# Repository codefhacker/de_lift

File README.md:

# de_lift
Site voor het bewaren van alle bestanden voor de lift

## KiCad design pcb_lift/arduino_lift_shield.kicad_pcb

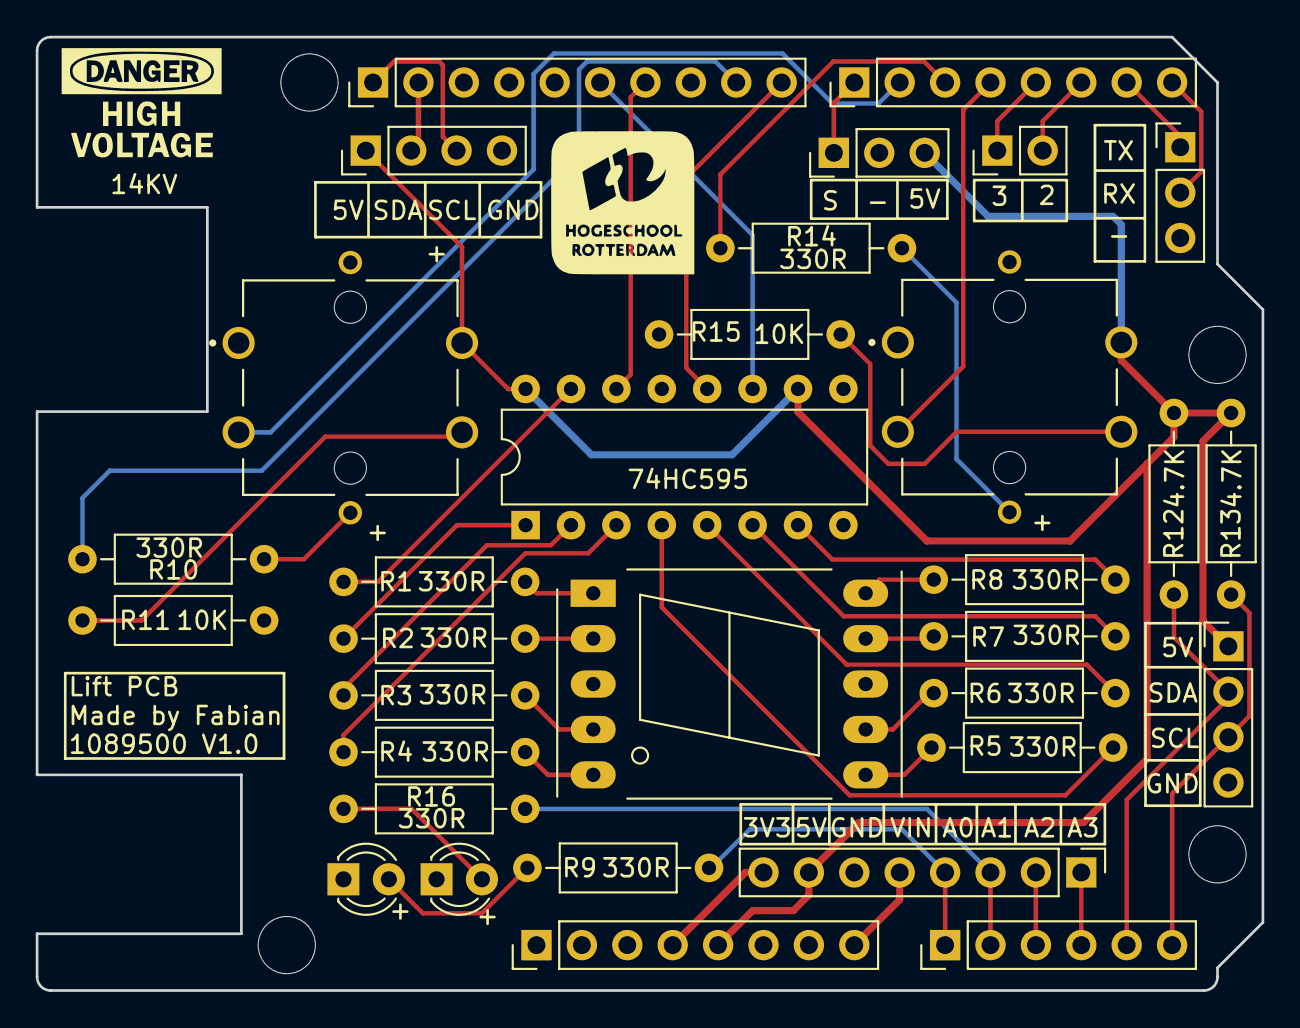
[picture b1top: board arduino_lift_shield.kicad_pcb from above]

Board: 2 copper layers, 68.6 x 53.3 mm, 36 parts (0 on the bottom side), 46 nets.

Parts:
D1, D2: LED; LED_D3.0mm
J1: Power; PinHeader_1x08_P2.54mm_Vertical
J2: Digital/PWM; PinHeader_1x10_P2.54mm_Vertical
J3: Analog; PinHeader_1x06_P2.54mm_Vertical
J4: Digital/PWM; PinHeader_1x08_P2.54mm_Vertical
J5, J10: Conn_01x04_Pin; PinHeader_1x04_P2.54mm_Vertical
J6, J9: Conn_01x03_Pin; PinHeader_1x03_P2.54mm_Vertical
J7: Conn_01x08_Pin; PinHeader_1x08_P2.54mm_Vertical
J11: Conn_01x02_Pin; PinHeader_1x02_P2.54mm_Vertical
MH1, MH2, MH3, MH4: MountingHole_3.2mm
R1, R2, R3, R4, R5, R6, R7, R8, R9, R10, R14, R16: 330R; R_Axial_DIN0207_L6.3mm_D2.5mm_P10.16mm_Horizontal
R11, R15: 10K; R_Axial_DIN0207_L6.3mm_D2.5mm_P10.16mm_Horizontal
R12, R13: 4.7K; R_Axial_DIN0207_L6.3mm_D2.5mm_P10.16mm_Horizontal
S1, S2: TSD1265; SW_TSD1265
U1: 74HC595; DIP-16_W7.62mm
U2: SM420561N; 7SegmentLED_LTS6760_LTS6780

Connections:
+3V3: J1.4, J7.8
+5V: J1.5, J5.1, J7.7, J9.3, J10.1, R12.2, R13.2, S1.D, S2.D, U1.10 (~SRCLR), U1.16 (VCC)
/2: J4.6, J11.2
/4: J4.4, S2.A
/7: J4.1, J9.1
/8: J2.10, U1.12 (RCLK)
/12: J2.6, U1.11 (SRCLK)
/*3: J4.5, J11.1
/*5: J4.3, R14.1
/*6: J4.2, S1.A
/*9: J2.9, R10.1
/*11: J2.7, U1.14 (SER)
/A0: J3.1, J7.4, R9.1
/A1: J3.2, J7.3, R16.1
/A2: J3.3, J7.2
/A3: J3.4, J7.1
/RX/0: J4.8, J6.2
/SCL2: J2.1, J5.3
/SCL/A5: J3.6, J10.3, R13.1
/SDA2: J2.2, J5.2
/SDA/A4: J3.5, J10.2, R12.1
/TX/1: J4.7, J6.1
GND: D1.1 (K), D2.1 (K), J1.6, J1.7, J2.4, J5.4, J6.3, J7.6, J9.2, J10.4, R11.2, R15.2, S1.F, S2.F, U1.8 (GND), U1.13 (~OE), U2.3 (CC), U2.8 (CC)
unnamed: D1.2 (A), R9.2
unnamed: D2.2 (A), R16.2
unnamed: R10.2, S1.E
unnamed: R11.1, S1.C
unnamed: R14.2, S2.E
unnamed: R15.1, S2.C
unnamed: R1.1, U1.15 (QA)
unnamed: R2.1, U1.1 (QB)
unnamed: R3.1, U1.2 (QC)
unnamed: R4.1, U1.3 (QD)
unnamed: R5.1, U1.4 (QE)
unnamed: R6.1, U1.5 (QF)
unnamed: R7.1, U1.6 (QG)
unnamed: R8.1, U1.7 (QH)
Pin_1: R1.2, U2.1 (E)
Pin_2: R2.2, U2.2 (D)
Pin_3: R3.2, U2.4 (C)
Pin_4: R4.2, U2.5 (DP)
Pin_5: R5.2, U2.6 (B)
Pin_6: R6.2, U2.7 (A)
Pin_7: R7.2, U2.9 (F)
Pin_8: R8.2, U2.10 (G)
VCC: J1.8, J7.5

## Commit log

2024-09-26 Create knop Arduino
2024-09-26 Rename knop Arduino to knop_led/knop_Arduino.ino
2024-10-10 Proof of concept interrupt
2024-10-17 prototype queue system
2024-10-17 determineDestination
2024-10-24 prot
2024-10-24 aaaa
2024-10-24 reworked without vectors
2024-10-24 Revert "Update main_master.ino"
    This reverts commit 14befe3b8252d7612847a0a98ab4e78e82f8f75f.
2024-10-24 [WIP] Movequeue 0.0.0.1
2024-11-11 Create Ontwerp_machinekamer
2024-11-11 Create PcbCase
2024-11-11 move function
2024-11-11 Create Trello
2024-11-11 Create Excel
2024-11-11 Update Excel
2024-11-11 queuing and moving proto v1
2024-11-11 typofix
2024-11-11 typofix2
2024-11-11 moretypofix
2024-11-11 Rename main_code_slave 2.zip to slave_full_package.zip
2024-11-11 version 1 gamma
2024-11-12 queueing
2024-11-13 Rename De lift | Trello.pdf to De lift Trello.pdf
